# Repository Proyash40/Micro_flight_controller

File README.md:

### Micro flight controller 
Okay so I couldn't find a flight controller small enough or light enough for what I needed, so I just designed one from scratch lol.

It uses a seeed XIAO and a bunch of tiny SMD parts (0805 mostly). it actually works and flies pretty smooth but u have to be okay with soldering things the size of a grain of rice.

---

### What is this?

Basically a 4 channel RC flight computer. it takes throttle, aileron, elevator, and rudder from an nRF24 radio, runs it through some PID math at 100Hz, checks the gyro, and moves the servos so your plane doesn't instantly do a death flip.

### Stuff u need to build this
### The BOM
---

| Name | Purpose | Quantity | Price (1 Unit) | Price Total(USD) | Links| 
| :-- | :-- | :-- | :-- | :-- | :-- |
| 4.7k smd resistor| I2C Pull-up for MPU6050  | 2     | $3.61    | $3.61   | [Link](https://robu.in/product/pro-range-resistor-assortment-kit?gbraid=0AAAAADvLFWev9HLp4sxOwY4NhUPUn_UtG&gad_source=1&gclid=CjwKCAjwhqfPBhBWEiwAZo196v5bzfSOsC9HW_fTPULaQ9_nrkw8cpucVvh93sHcz886qdtSFOGdzhoCiaEQAvD_BwE&gad_campaignid=17413441824)|
| AMS1117 | Power Stability | 1 | $0.1 | $0.1 | [link](https://robu.in/product/ams1117-5-0-kexin-800ma-fixed-5v-positive-electrode-18v-sot-223-4-voltage-regulators-linear-low-drop-out-ldo-regulators-rohs?gclid=CjwKCAjwhqfPBhBWEiwAZo196rn1-FbjdC99BRNd9EsXMXFG3gaLsCGdJgY27B3j1U-KVRJFFhwOmRoCjTQQAvD_BwE&gbraid=0AAAAADvLFWcFOfMDkpSzIEVzy6CGMtIqJ&gad_campaignid=17427802703&gad_source=1) |
| MPU6050 | 3 axis gyro + accelerometer | 1 | $2.55 | $2.55 | [link](https://quartzcomponents.com/products/mpu-6050-3-axis-gyro-accelerometer-ic-tdk-invensense-qfn-24-smd-package?variant=45045443920106&country=IN&currency=INR&utm_medium=product_sync&utm_source=google&utm_content=sag_organic&utm_campaign=sag_organic&srsltid=AfmBOopUSjOK5jLivqVKUFYTqOvJck_zu4O2Uv3mEJbdvORH596ugewjbbI) |
| Seeed studio XIAO ESP32 supermini C3 | The main brain | 1 | $9.56 | $9.56 | [Link](https://robu.in/product/seeed-studio-xiao-esp32s3-2-4ghz-wifi-ble-5-0?gbraid=0AAAAADvLFWcFOfMDkpSzIEVzy6CGMtIqJ&gad_campaignid=17427802703&gad_source=1&gclid=CjwKCAjwhqfPBhBWEiwAZo196qhD7iCgQVOGc9_I62SJPdePZ3dxGMH-cF4la4ANgsBjqeiDQebpEhoCmOUQAvD_BwE) |
| PCB print | Holding all the components together | 1 | $ 3 | $3 | [Link](https://cart.jlcpcb.com/quote)
| Capacitor 0.1uF (100nF) 0805| Decoupling for MPU6050 | 3 | -- | -- | I'd recomend buying it offline |
| Capacitor 2.2nF 0805 | MPU6050 Charge Pump | 1 |  -- | -- | I'd recomend buying it offline |
| Capacitor 10uF 0805 | AMS1117 Input Filter| 2 |  -- | -- | I'd recomend buying it offline |
| Capacitor 100uF 1210 | nRF24 Power Buffer* | 2 | -- | -- | I'd recomend buying it offline |

### IMPORTANT RANT ABOUT SOLDER

Do NOT use cheap 60/40 or 35/65 solder for this. The vibrations from the drone motors will crack your joints. buy actual 63/37 (Tin/Lead) Rosin Core 0.5mm wire. It solidifies instantly and doesn't get mushy. Soldron is fine. Just don't buy the cheap unbranded tubes.

### Software stuff

The code is in C++. don't use the normal arduino IDE for this, it sucks for complex stuff. Use VS Code + PlatformIO.

### Libraries u need:

RF24 (for the radio)

MPU6050_light (so much better than writing custom kalman filters)

PID_v1 (for the stabilization math)

---

Note: The loop is locked at 100Hz so the servos don't twitch themselves to death. The I2C is boosted to 400kHz so the gyro reads fast enough.

---

### How to fly 

1) Turn on radio.

2) Plug in battery.

3) DO NOT touch the plane for like 3 seconds while the MPU6050 calibrates.

4) Arm the throttle (push it up past 1050us).

5) Pray your PID tuning is right.

---

### Images

---
If u haven't flown any rc before, I'd recomend to let someone experienced fly it first unless you want to destroy all your hard work on  the first flight.

---
(Disclaimer: if u copy my PID values and your plane nosedives into a tree, that's on u. tune it yourself for your airframe).

Have fun ✌️

### ~GODSPEED

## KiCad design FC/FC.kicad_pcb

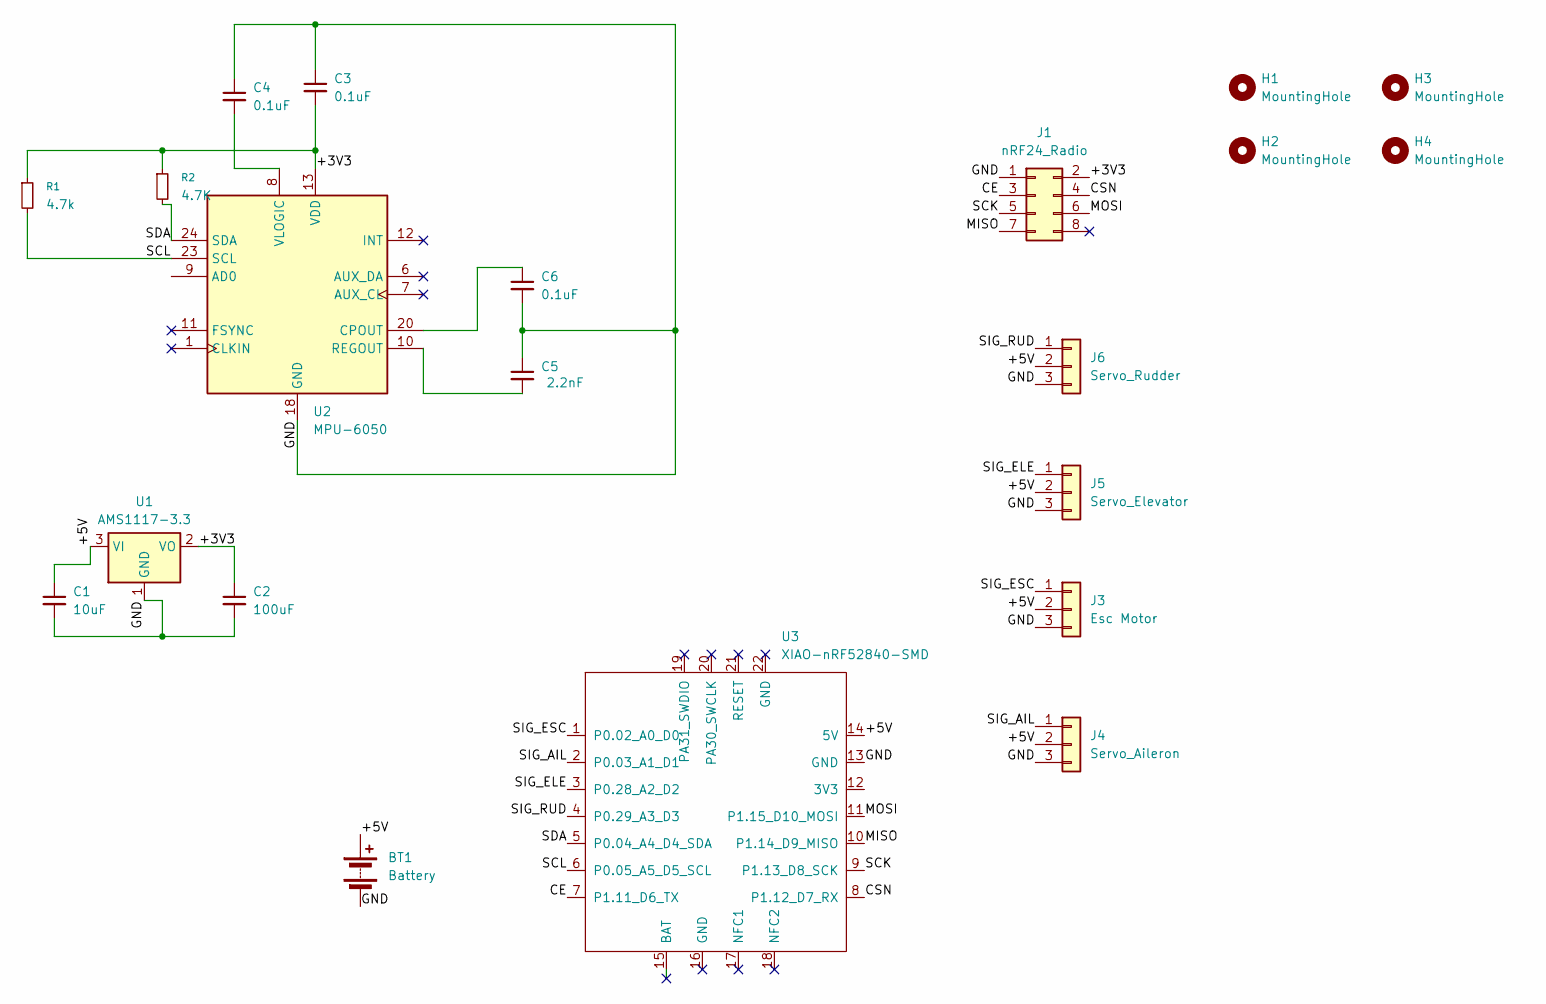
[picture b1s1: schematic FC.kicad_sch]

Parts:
BT1: Battery; MountingHole_2.2mm_M2
C1: 10uF; C_0805_2012Metric_Pad1.18x1.45mm_HandSolder
C2: 100uF; C_1210_3225Metric_Pad1.33x2.70mm_HandSolder
C3, C4, C6: 0.1uF; C_0805_2012Metric_Pad1.18x1.45mm_HandSolder
C5: 2.2nF; C_0805_2012Metric_Pad1.18x1.45mm_HandSolder
H1, H2, H3, H4: MountingHole; MountingHole_2.2mm_M2
J1: nRF24_Radio; PinSocket_2x04_P2.54mm_Vertical
J3: Esc Motor; PinHeader_1x03_P2.54mm_Vertical
J4: Servo_Aileron; PinHeader_1x03_P2.54mm_Vertical
J5: Servo_Elevator; PinHeader_1x03_P2.54mm_Vertical
J6: Servo_Rudder; PinHeader_1x03_P2.54mm_Vertical
R1: 4.7k; R_0805_2012Metric_Pad1.20x1.40mm_HandSolder
R2: 4.7K; R_0805_2012Metric_Pad1.20x1.40mm_HandSolder
U1: AMS1117-3.3; SOT-223-3_TabPin2
U2: MPU-6050; InvenSense_QFN-24_4x4mm_P0.5mm
U3: XIAO-nRF52840-SMD; MODULE_102010428

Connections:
/+3V3: C2.1, C3.2, J1.2, R1.1, R2.1, U1.2 (VO), U2.13 (VDD)
/+5V: BT1.1 (+), C1.1, J3.2, J4.2, J5.2, J6.2, U1.3 (VI), U3.14 (5V)
/<NO NET>: J5.1, U3.3 (P0.28_A2_D2)
/CE: J1.3, U3.7 (P1.11_D6_TX)
/CSN: J1.4, U3.8 (P1.12_D7_RX)
/GND: BT1.2 (-), C1.2, C2.2, C3.1, C4.1, C5.1, C6.2, J1.1, J3.3, J4.3, J5.3, J6.3, U1.1 (GND), U2.18 (GND), U3.13 (GND)
/MISO: J1.7, U3.10 (P1.14_D9_MISO)
/MOSI: J1.6, U3.11 (P1.15_D10_MOSI)
/SCK: J1.5, U3.9 (P1.13_D8_SCK)
/SCL: R1.2, U2.23 (SCL), U3.6 (P0.05_A5_D5_SCL)
/SDA: R2.2, U2.24 (SDA), U3.5 (P0.04_A4_D4_SDA)
/SIG_AIL: J4.1, U3.2 (P0.03_A1_D1)
/SIG_ESC: J3.1, U3.1 (P0.02_A0_D0)
/SIG_RUD: J6.1, U3.4 (P0.29_A3_D3)
unnamed: C6.1, U2.20 (CPOUT)
unnamed: C5.2, U2.10 (REGOUT)
unnamed: C4.2, U2.8 (VLOGIC)

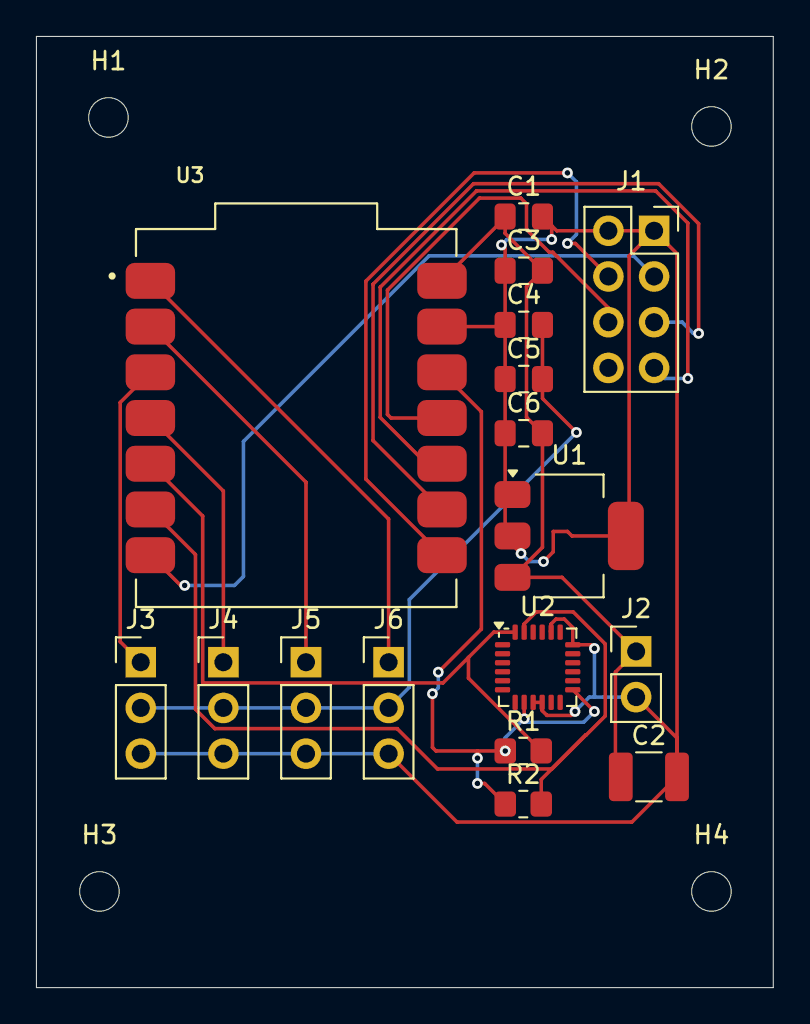
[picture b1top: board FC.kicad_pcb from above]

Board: 2 copper layers, 40.9 x 52.8 mm, 21 parts (0 on the bottom side), 17 nets.

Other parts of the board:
J2: Conn_01x02; PinHeader_1x02_P2.54mm_Vertical

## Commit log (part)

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2026-04-24 Add files via upload
    Please note
    In this CSV, I've not included the Capacitors, and the pcb print.
2026-04-28 Add more images to README
    Added additional images to the README for better visualization.
